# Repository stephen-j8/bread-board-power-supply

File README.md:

# bread-board-power-supply

## Project Overview
My second PCB Project (Bread-board-power-supply), designed in KiCad

## Circuit Details
- Input Voltage : 12V
- Output Voltage : 5V or 3.3V ( BY using the voltage regulators )
- Connected to LED as power indicator
- Capacitors are connected to filter noice
- Resistors are connected for adjustment and protect the components

## Tools Used
- KiCad ( version 0.10 ) : For design the board ( Schematic and PCB Layout)
- JLCPCB : To order the physical board

## Files included
- /Gerber : All gerber Files
- /pdf : Schematic File
- /png : All screenshots ( Schematic file, PCB file, Gerber file, 3D model file )
- /csv : Bill Of Materials
- /pcb : PCB Layout File
- /sch : Schematic File
- /pro : main accumulation of files

## PCB Preveiw

## Bill Of Materials
Kindly see the .CSV File

## Status
- Schematic Completed
- PCB Layout Completed
- Gerber Files Generated
- PCB Ordered from JLCPCB
- Physical board awaited

## Author
STEPHEN- EEE Engineer

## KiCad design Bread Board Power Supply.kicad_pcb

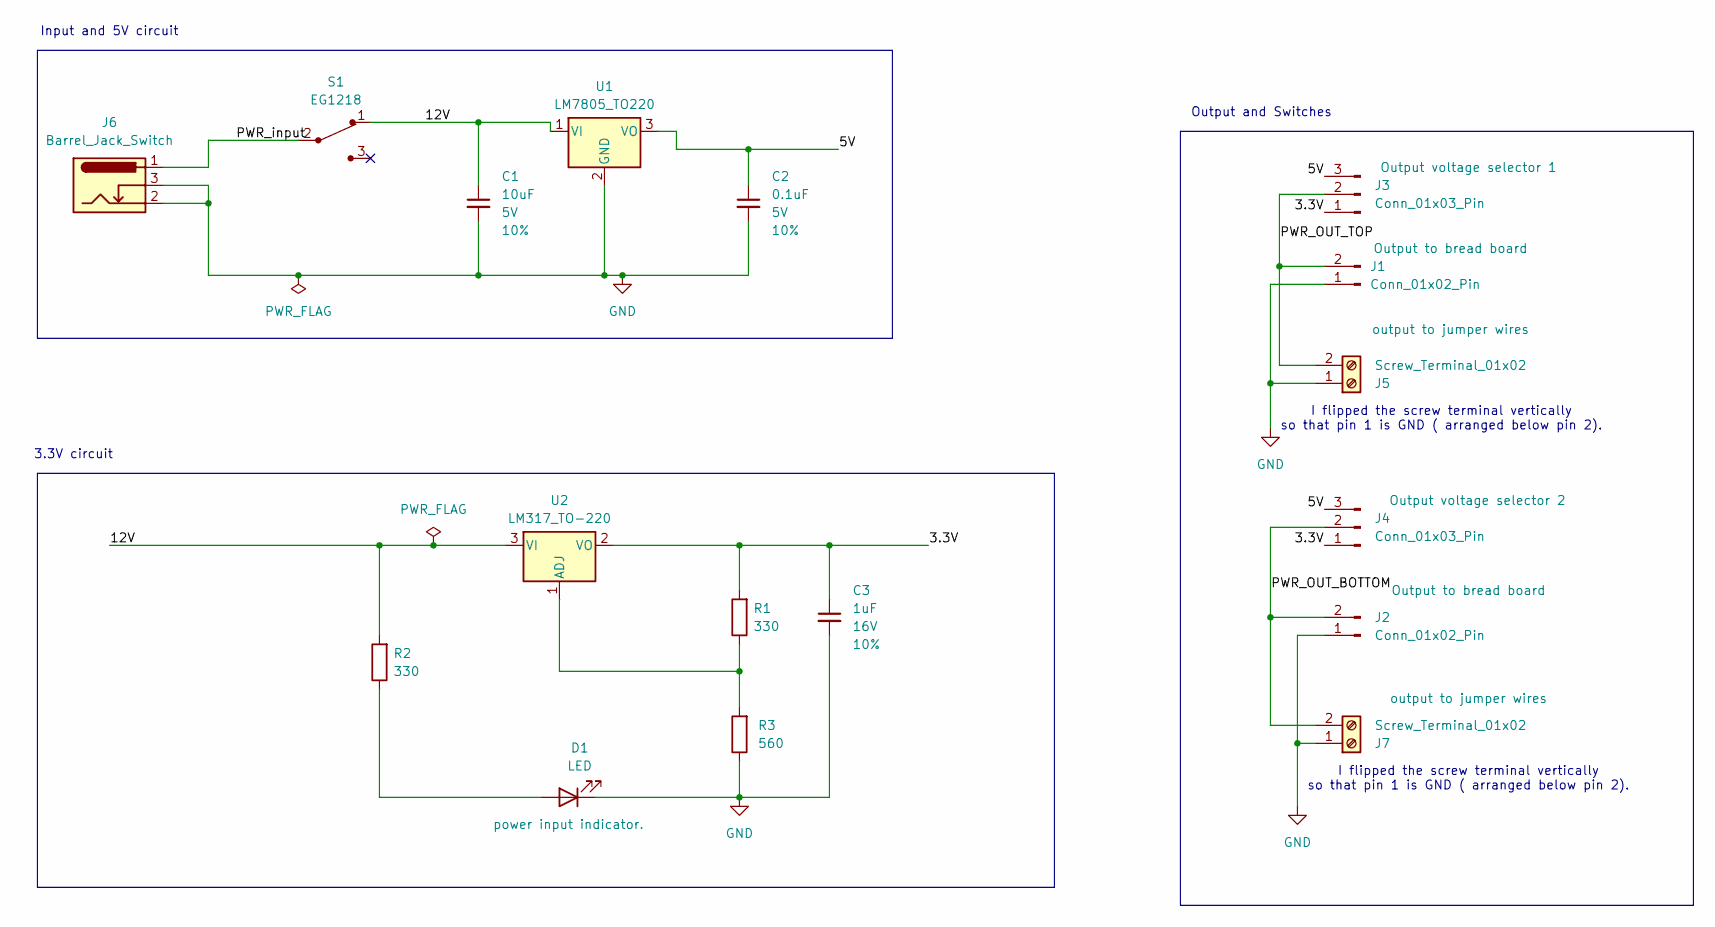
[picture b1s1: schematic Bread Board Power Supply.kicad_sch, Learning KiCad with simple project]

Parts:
C1: 10uF; C_Disc_D3.0mm_W1.6mm_P2.50mm; Voltage 5V; Tolerance 10%
C2: 0.1uF; C_Disc_D3.0mm_W1.6mm_P2.50mm; Voltage 5V; Tolerance 10%
C3: 1uF; C_Disc_D3.0mm_W1.6mm_P2.50mm; Voltage 16V; Tolerance 10%
D1: LED; LED_D5.0mm
J1, J2: Conn_01x02_Pin; PinHeader_1x02_P2.54mm_Vertical
J3, J4: Conn_01x03_Pin; PinHeader_1x03_P2.54mm_Vertical
J5, J7: Screw_Terminal_01x02; TerminalBlock_MaiXu_MX126-5.0-02P_1x02_P5.00mm
J6: Barrel_Jack_Switch; BarrelJack_Horizontal
R1, R2: 330; R_Axial_DIN0204_L3.6mm_D1.6mm_P7.62mm_Horizontal
R3: 560; R_Axial_DIN0204_L3.6mm_D1.6mm_P7.62mm_Horizontal
S1: EG1218; Switch_Slide_11.6x4mm_EG1218; MPN EG1218; Digi-Key_PN EG1903-ND
U1: LM7805_TO220; TO-220-3_Vertical
U2: LM317_TO-220; TO-220-3_Vertical

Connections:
/3.3V: C3.1, J3.1, J4.1, R1.2, U2.2 (VO)
/5V: C2.1, J3.3, J4.3, U1.3 (VO)
/12V: C1.1, R2.2, S1.1, U1.1 (VI), U2.3 (VI)
/PWR_OUT_BOTTOM: J2.2, J4.2, J7.2
/PWR_OUT_TOP: J1.2, J3.2, J5.2
/PWR_input: J6.1, S1.2
GND: C1.2, C2.2, C3.2, D1.1 (K), J1.1, J2.1, J5.1, J6.2, J6.3, J7.1, R3.1, U1.2 (GND)
unnamed: D1.2 (A), R2.1
unnamed: R1.1, R3.2, U2.1 (ADJ)

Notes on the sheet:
Output and Switches
Input and 5V circuit
3.3V circuit
I flipped the screw terminal vertically so that pin 1 is GND ( arranged below pin 2).

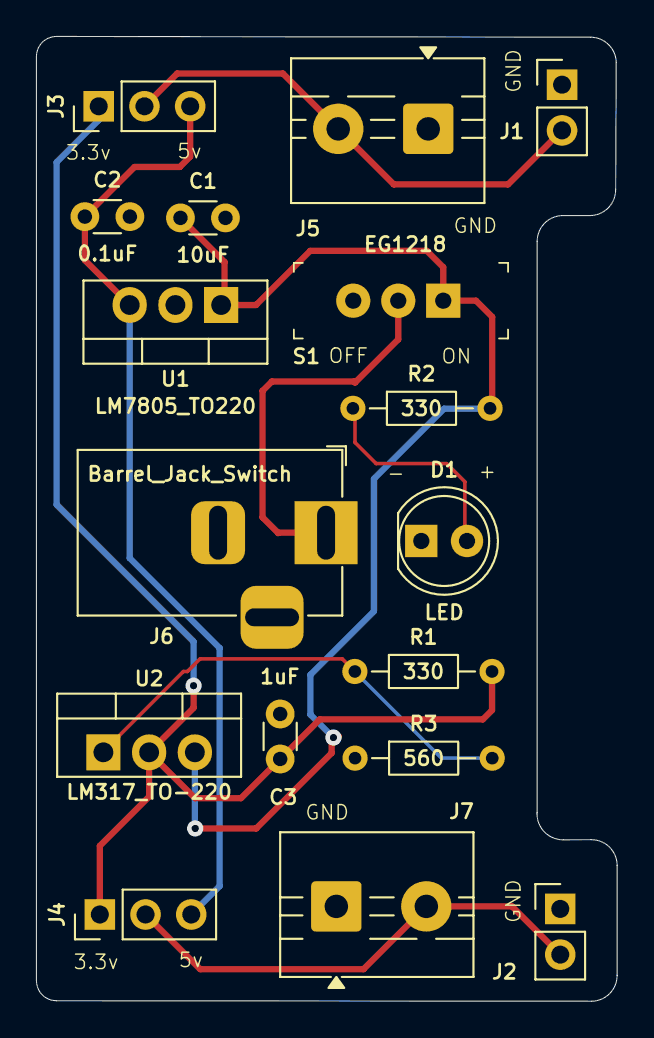
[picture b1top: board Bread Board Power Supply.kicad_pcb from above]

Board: 2 copper layers, 32.3 x 53.6 mm, 17 parts (0 on the bottom side), 9 nets.

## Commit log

2026-06-04 Create LICENSE
